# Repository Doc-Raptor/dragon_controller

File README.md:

This is a controller-board for 3d printers from china which are based on the anet printers and using an 8-bit board with 
on-board stepper driver and sometimes no fuse-protection (and no thermal-run-away).
This board is a low cost replacement with an stm32f103ret and socketed stepper drivers.
It is also capable of runnung from 24v.

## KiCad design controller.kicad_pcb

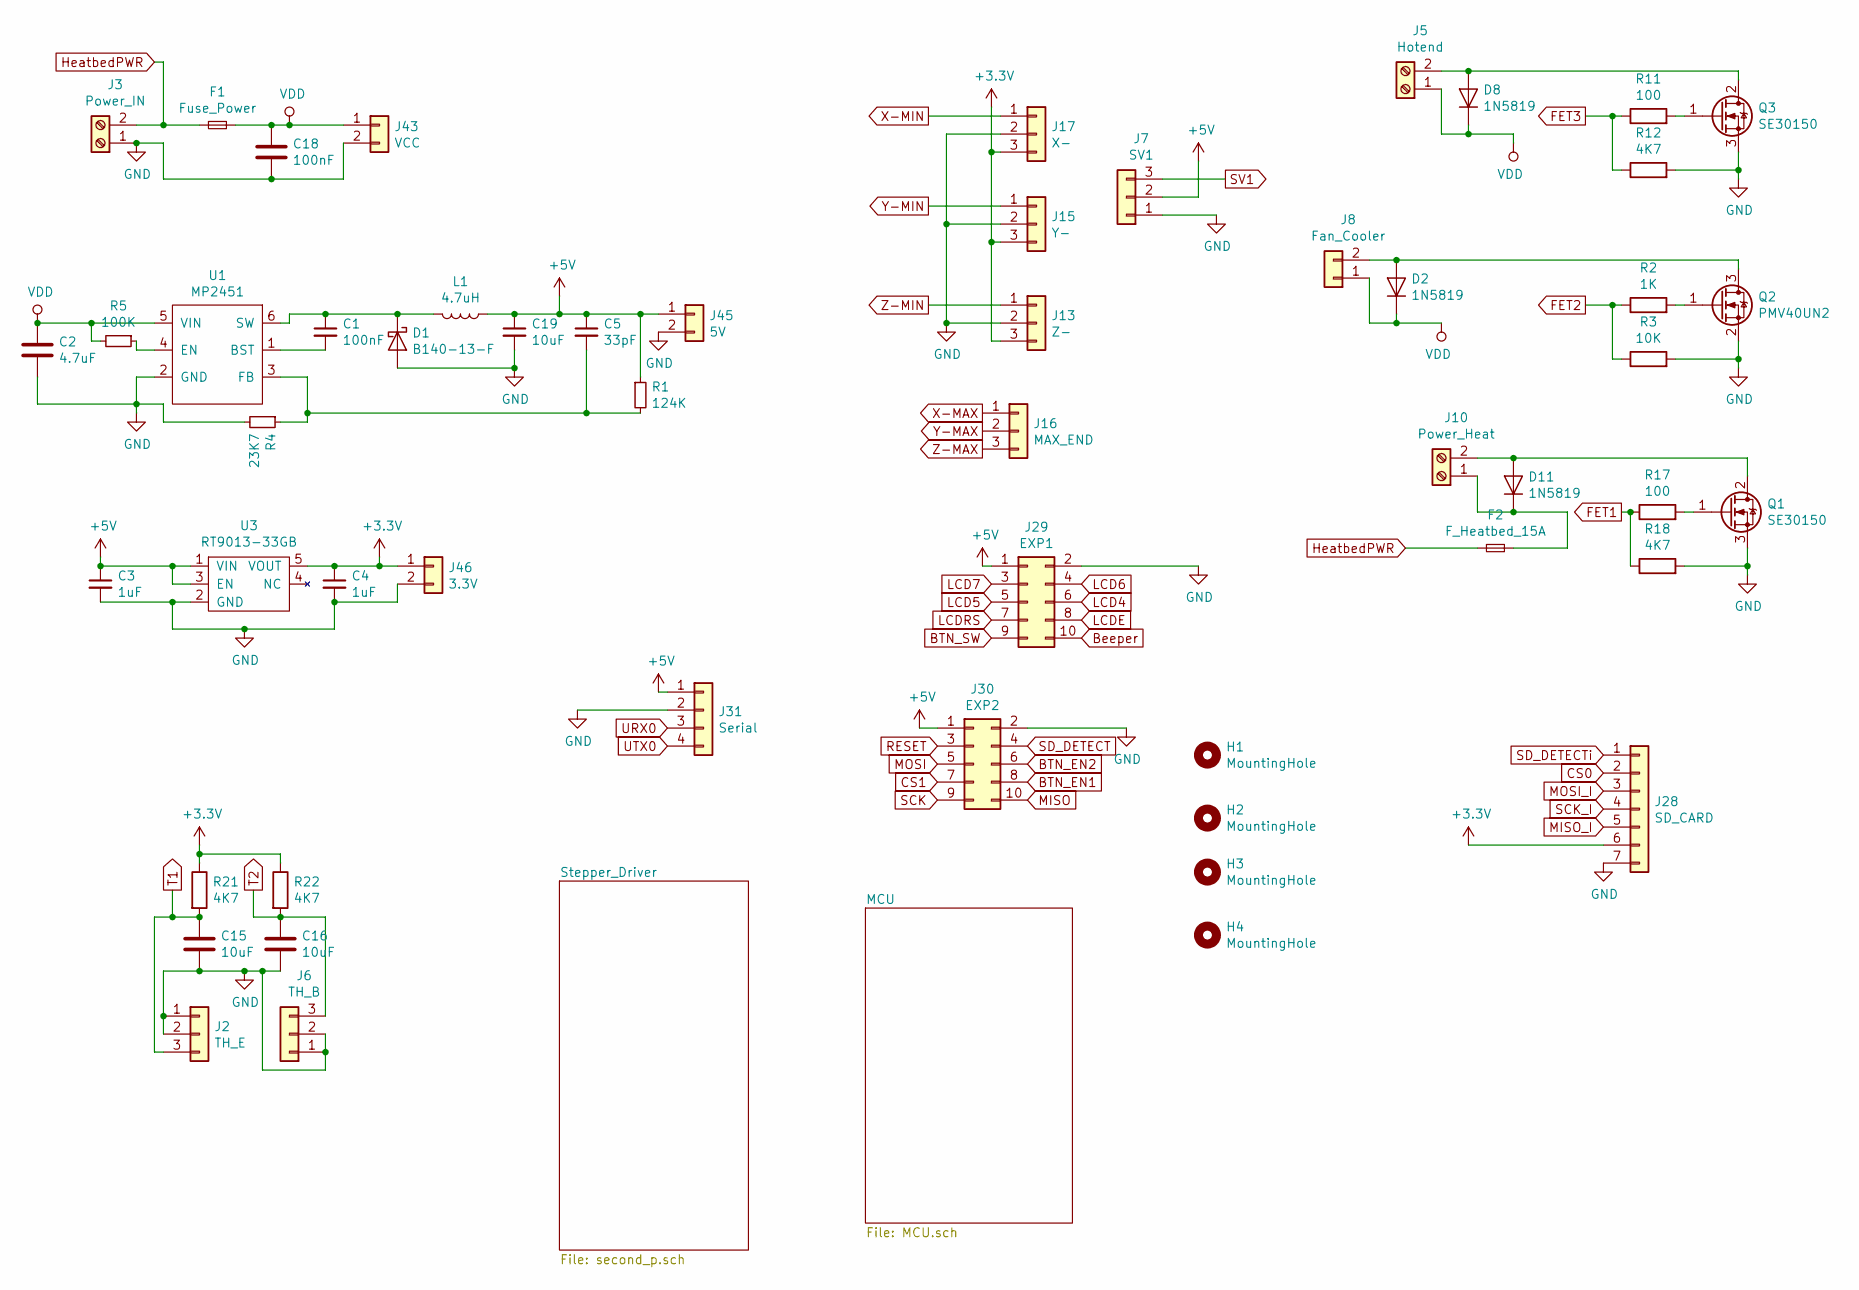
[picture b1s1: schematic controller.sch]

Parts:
C1, C18: 100nF; C_1206_3216Metric
C2: 4.7uF; C_1206_3216Metric
C3, C4: 1uF; C_0805_2012Metric
C5: 33pF; C_0603_1608Metric
C15, C16, C19: 10uF; C_1206_3216Metric
D1: B140-13-F; D_SMA
D2, D8, D11: 1N5819; D_SOD-123
F1: Fuse_Power; Fuseholder_Blade_ATO_Littelfuse_Pudenz_2_Pin
F2: F_Heatbed_15A; Fuseholder_Blade_ATO_Littelfuse_Pudenz_2_Pin
H1, H2, H3, H4: MountingHole; MountingHole_3.2mm_M3
J2: TH_E; PinHeader_1x03_P2.54mm_Vertical
J3: Power_IN; PhoenixContact_GMSTBVA_2,5_2-G-7,62_1x02_P7.62mm_Vertical
J5: Hotend; PhoenixContact_MCV_1,5_2-G-5.08_1x02_P5.08mm_Vertical
J6: TH_B; PinHeader_1x03_P2.54mm_Vertical
J7: SV1; PinHeader_1x03_P2.54mm_Vertical
J8: Fan_Cooler; PinHeader_1x02_P2.54mm_Vertical
J10: Power_Heat; PhoenixContact_GMSTBVA_2,5_2-G-7,62_1x02_P7.62mm_Vertical
J13: Z-; PinHeader_1x03_P2.54mm_Vertical
J15: Y-; PinHeader_1x03_P2.54mm_Vertical
J16: MAX_END; PinHeader_1x03_P2.54mm_Vertical
J17: X-; PinHeader_1x03_P2.54mm_Vertical
J28: SD_CARD; PinHeader_1x07_P2.54mm_Vertical
J29: EXP1; PinHeader_2x05_P2.54mm_Vertical
J30: EXP2; PinHeader_2x05_P2.54mm_Vertical
J31: Serial; PinHeader_1x04_P2.54mm_Vertical
J43: VCC; PinHeader_1x02_P2.54mm_Vertical
J45: 5V; PinHeader_1x02_P2.54mm_Vertical
J46: 3.3V; PinHeader_1x02_P2.54mm_Vertical
L1: 4.7uH; L_1812_4532Metric
Q1, Q3: SE30150; TO-263-3_TabPin2
Q2: PMV40UN2; SOT-23
R1: 124K; R_1206_3216Metric
R2: 1K; R_1206_3216Metric
R3: 10K; R_1206_3216Metric
R4: 23K7; R_1206_3216Metric
R5: 100K; R_1206_3216Metric
R11, R17: 100; R_1206_3216Metric
R12, R18, R21, R22: 4K7; R_1206_3216Metric
U1: MP2451; SOT-23-6
U3: RT9013-33GB; SOT-23-5

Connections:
+3V3: C4.1, J13.3, J15.3, J17.3, J28.6, J46.1, R21.1, R22.1, U3.5 (VOUT); also elsewhere on the board
+5V: C3.1, C5.1, C19.1, J7.2, J29.1, J30.1, J31.1, J45.1, L1.1, R1.1, U3.1 (VIN), U3.3 (EN)
BTN_EN1: J30.8; also elsewhere on the board
BTN_EN2: J30.6; also elsewhere on the board
BTN_SW: J29.9; also elsewhere on the board
Beeper: J29.10; also elsewhere on the board
CS0: J28.2; also elsewhere on the board
CS1: J30.7; also elsewhere on the board
FET1: R17.1, R18.1; also elsewhere on the board
FET2: R2.1, R3.1; also elsewhere on the board
FET3: R11.1, R12.1; also elsewhere on the board
GND: C2.2, C3.2, C4.2, C15.2, C16.2, C18.2, C19.2, D1.2 (A), J2.1, J2.2, J3.1, J6.1, J6.2, J7.1, J13.2, J15.2, J17.2, J28.7, J29.2, J30.2, J31.2, J43.2, J45.2, J46.2, Q1.3 (S), Q2.2 (S), Q3.3 (S), R3.2, R4.2, R12.2, R18.2, U1.2 (GND), U3.2 (GND); also elsewhere on the board
HeatbedPWR: F1.1, F2.1, J3.2
LCD4: J29.6; also elsewhere on the board
LCD5: J29.5; also elsewhere on the board
LCD6: J29.4; also elsewhere on the board
LCD7: J29.3; also elsewhere on the board
LCDE: J29.8; also elsewhere on the board
LCDRS: J29.7; also elsewhere on the board
MISO: J30.10; also elsewhere on the board
MISO_I: J28.5; also elsewhere on the board
MOSI: J30.5; also elsewhere on the board
MOSI_I: J28.3; also elsewhere on the board
unnamed: C1.1, D1.1 (K), L1.2, U1.6 (SW)
unnamed: C1.2, U1.1 (BST)
unnamed: C5.2, R1.2, R4.1, U1.3 (FB)
unnamed: D2.2 (A), J8.2, Q2.3 (D)
unnamed: D8.2 (A), J5.2, Q3.2 (D)
unnamed: D11.1 (K), F2.2, J10.1
unnamed: D11.2 (A), J10.2, Q1.2 (D)
unnamed: Q1.1 (G), R17.2
unnamed: Q2.1 (G), R2.2
unnamed: Q3.1 (G), R11.2
unnamed: R5.1, U1.4 (EN)
RESET: J30.3; also elsewhere on the board
SCK: J30.9; also elsewhere on the board
SCK_I: J28.4; also elsewhere on the board
SD_DETECT: J30.4; also elsewhere on the board
SD_DETECTi: J28.1; also elsewhere on the board
SV1: J7.3; also elsewhere on the board
T1: C15.1, J2.3, R21.2; also elsewhere on the board
T2: C16.1, J6.3, R22.2; also elsewhere on the board
URX0: J31.3; also elsewhere on the board
UTX0: J31.4; also elsewhere on the board
VDD: C2.1, C18.1, D2.1 (K), D8.1 (K), F1.2, J5.1, J8.1, J43.1, R5.2, U1.5 (VIN); also elsewhere on the board
X-MAX: J16.1; also elsewhere on the board
X-MIN: J17.1; also elsewhere on the board
Y-MAX: J16.2; also elsewhere on the board
Y-MIN: J15.1; also elsewhere on the board
Z-MAX: J16.3; also elsewhere on the board
Z-MIN: J13.1; also elsewhere on the board

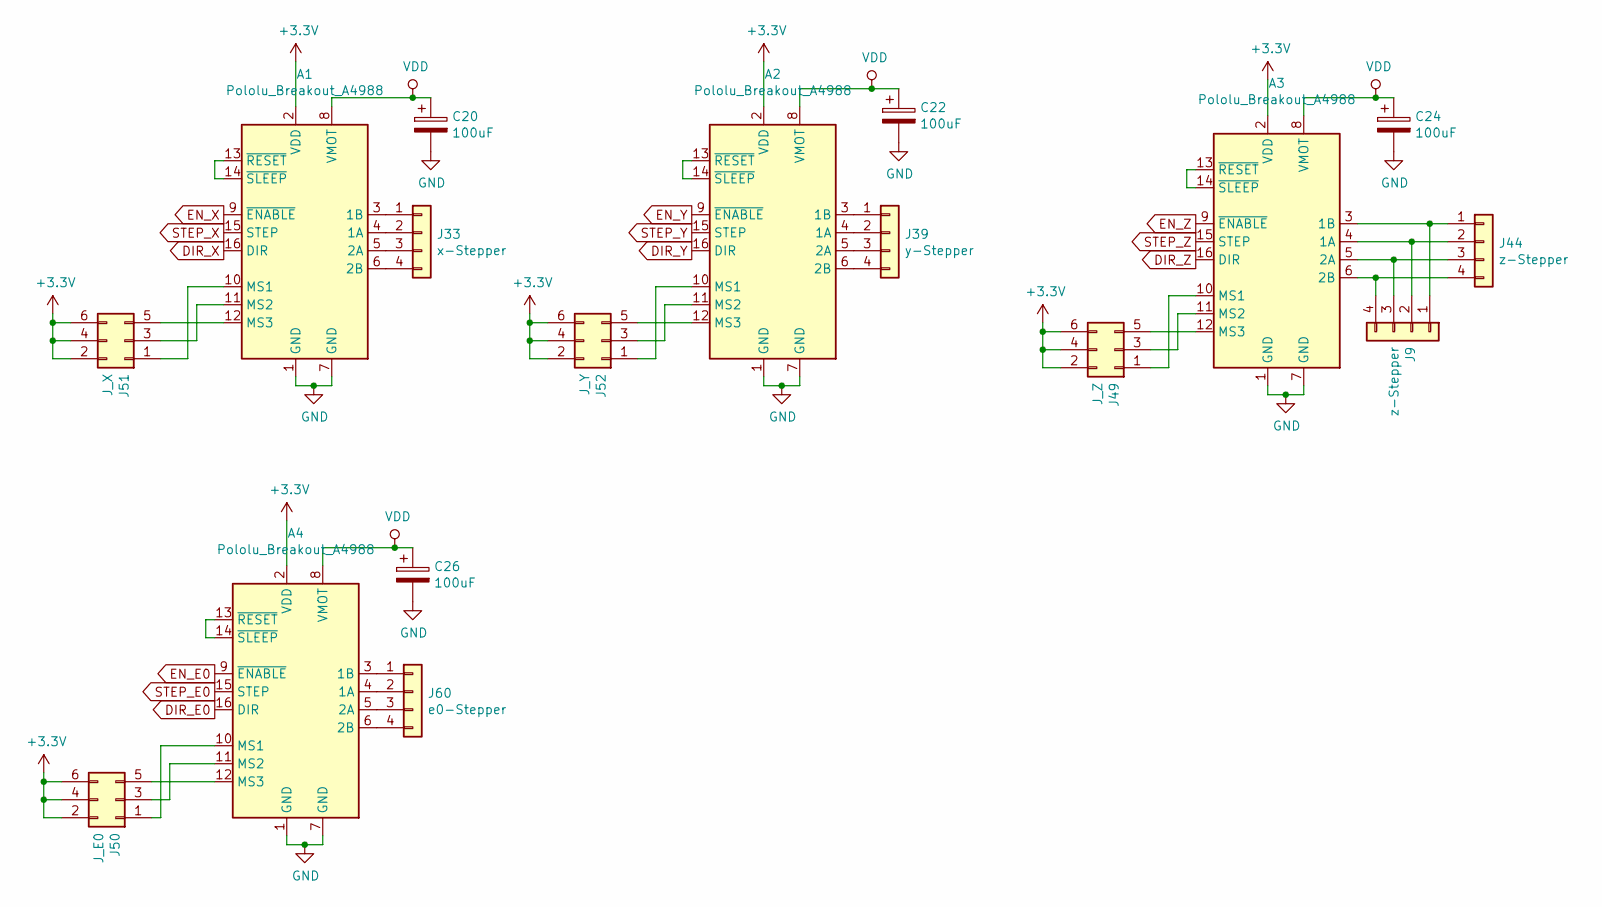
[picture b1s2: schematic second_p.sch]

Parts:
A1, A2, A3, A4: Pololu_Breakout_A4988; Pololu_Breakout-16_15.2x20.3mm
C20, C22, C24, C26: 100uF; CP_Elec_6.3x7.7
J9, J44: z-Stepper; PinHeader_1x04_P2.54mm_Vertical
J33: x-Stepper; PinHeader_1x04_P2.54mm_Vertical
J39: y-Stepper; PinHeader_1x04_P2.54mm_Vertical
J49: J_Z; PinHeader_2x03_P2.54mm_Vertical
J50: J_E0; PinHeader_2x03_P2.54mm_Vertical
J51: J_X; PinHeader_2x03_P2.54mm_Vertical
J52: J_Y; PinHeader_2x03_P2.54mm_Vertical
J60: e0-Stepper; PinHeader_1x04_P2.54mm_Vertical

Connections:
+3V3: A1.2 (VDD), A2.2 (VDD), A3.2 (VDD), A4.2 (VDD), J49.2, J49.4, J49.6, J50.2, J50.4, J50.6, J51.2, J51.4, J51.6, J52.2, J52.4, J52.6; also elsewhere on the board
DIR_E0: A4.16 (DIR); also elsewhere on the board
DIR_X: A1.16 (DIR); also elsewhere on the board
DIR_Y: A2.16 (DIR); also elsewhere on the board
DIR_Z: A3.16 (DIR); also elsewhere on the board
EN_E0: A4.9 (~ENABLE); also elsewhere on the board
EN_X: A1.9 (~ENABLE); also elsewhere on the board
EN_Y: A2.9 (~ENABLE); also elsewhere on the board
EN_Z: A3.9 (~ENABLE); also elsewhere on the board
GND: A1.1 (GND), A1.7 (GND), A2.1 (GND), A2.7 (GND), A3.1 (GND), A3.7 (GND), A4.1 (GND), A4.7 (GND), C20.2, C22.2, C24.2, C26.2; also elsewhere on the board
unnamed: A1.3 (1B), J33.1
unnamed: A1.4 (1A), J33.2
unnamed: A1.5 (2A), J33.3
unnamed: A1.6 (2B), J33.4
unnamed: A1.10 (MS1), J51.1
unnamed: A1.11 (MS2), J51.3
unnamed: A1.12 (MS3), J51.5
unnamed: A1.13 (~RESET), A1.14 (~SLEEP)
unnamed: A2.3 (1B), J39.1
unnamed: A2.4 (1A), J39.2
unnamed: A2.5 (2A), J39.3
unnamed: A2.6 (2B), J39.4
unnamed: A2.10 (MS1), J52.1
unnamed: A2.11 (MS2), J52.3
unnamed: A2.12 (MS3), J52.5
unnamed: A2.13 (~RESET), A2.14 (~SLEEP)
unnamed: A3.3 (1B), J9.1, J44.1
unnamed: A3.4 (1A), J9.2, J44.2
unnamed: A3.5 (2A), J9.3, J44.3
unnamed: A3.6 (2B), J9.4, J44.4
unnamed: A3.10 (MS1), J49.1
unnamed: A3.11 (MS2), J49.3
unnamed: A3.12 (MS3), J49.5
unnamed: A3.13 (~RESET), A3.14 (~SLEEP)
unnamed: A4.3 (1B), J60.1
unnamed: A4.4 (1A), J60.2
unnamed: A4.5 (2A), J60.3
unnamed: A4.6 (2B), J60.4
unnamed: A4.10 (MS1), J50.1
unnamed: A4.11 (MS2), J50.3
unnamed: A4.12 (MS3), J50.5
unnamed: A4.13 (~RESET), A4.14 (~SLEEP)
STEP_E0: A4.15 (STEP); also elsewhere on the board
STEP_X: A1.15 (STEP); also elsewhere on the board
STEP_Y: A2.15 (STEP); also elsewhere on the board
STEP_Z: A3.15 (STEP); also elsewhere on the board
VDD: A1.8 (VMOT), A2.8 (VMOT), A3.8 (VMOT), A4.8 (VMOT), C20.1, C22.1, C24.1, C26.1; also elsewhere on the board

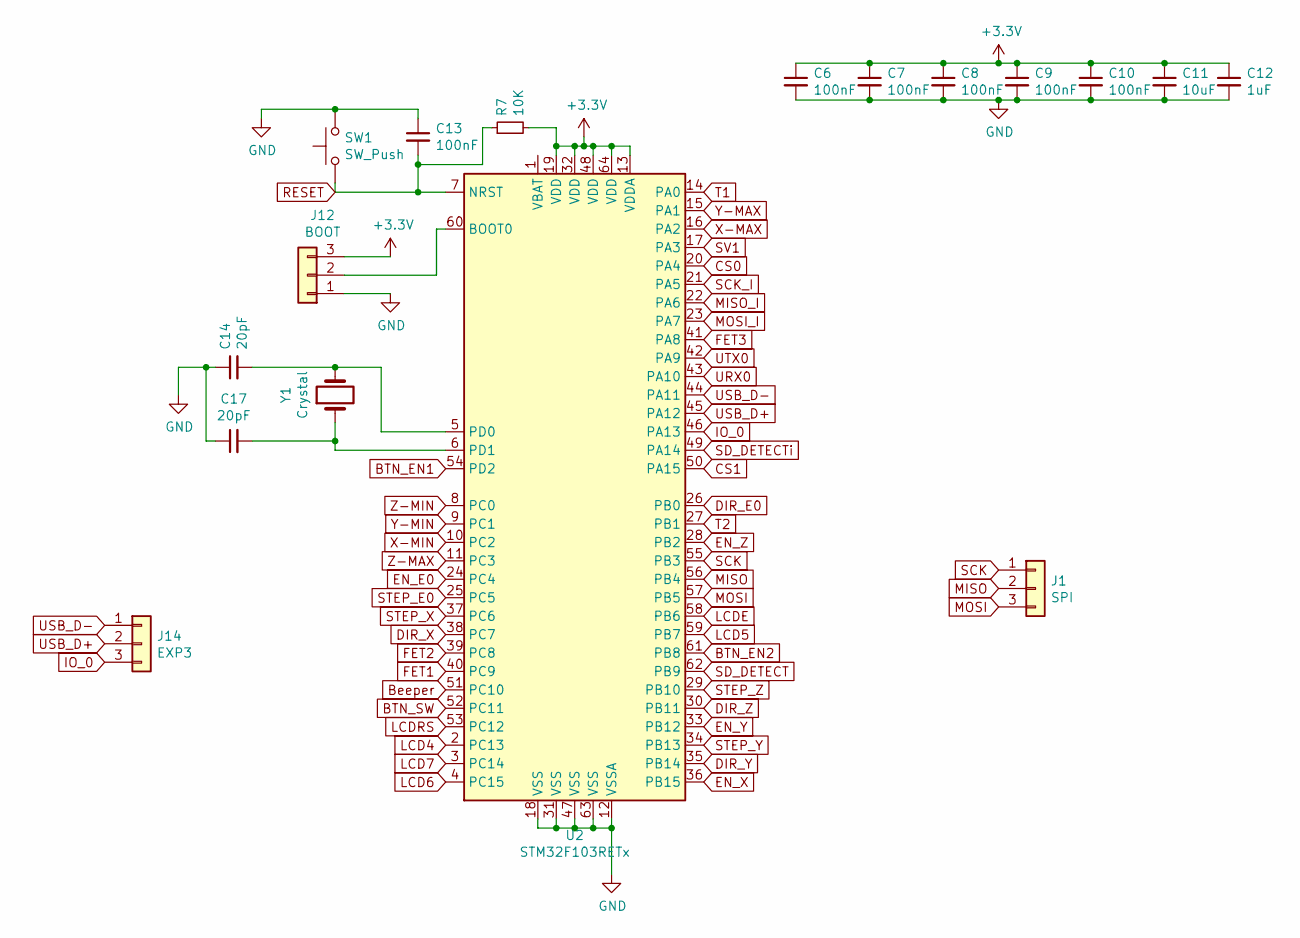
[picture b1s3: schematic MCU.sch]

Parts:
C6, C7, C8, C9, C10, C13: 100nF; C_1206_3216Metric
C11: 10uF; C_1206_3216Metric
C12: 1uF; C_0805_2012Metric
C14, C17: 20pF; C_0603_1608Metric
J1: SPI; PinHeader_1x03_P2.54mm_Vertical
J12: BOOT; PinHeader_1x03_P2.54mm_Vertical
J14: EXP3; PinHeader_1x03_P2.54mm_Vertical
R7: 10K; R_1206_3216Metric
SW1: SW_Push; SW_Push_SPST_NO_Alps_SKRK
U2: STM32F103RETx; LQFP-64_10x10mm_P0.5mm
Y1: Crystal; Crystal_SMD_5032-2Pin_5.0x3.2mm

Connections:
+3V3: C6.1, C7.1, C8.1, C9.1, C10.1, C11.1, C12.1, J12.3, R7.2, U2.13 (VDDA), U2.19 (VDD), U2.32 (VDD), U2.48 (VDD), U2.64 (VDD); also elsewhere on the board
BTN_EN1: U2.54 (PD2); also elsewhere on the board
BTN_EN2: U2.61 (PB8); also elsewhere on the board
BTN_SW: U2.52 (PC11); also elsewhere on the board
Beeper: U2.51 (PC10); also elsewhere on the board
CS0: U2.20 (PA4); also elsewhere on the board
CS1: U2.50 (PA15); also elsewhere on the board
DIR_E0: U2.26 (PB0); also elsewhere on the board
DIR_X: U2.38 (PC7); also elsewhere on the board
DIR_Y: U2.35 (PB14); also elsewhere on the board
DIR_Z: U2.30 (PB11); also elsewhere on the board
EN_E0: U2.24 (PC4); also elsewhere on the board
EN_X: U2.36 (PB15); also elsewhere on the board
EN_Y: U2.33 (PB12); also elsewhere on the board
EN_Z: U2.28 (PB2); also elsewhere on the board
FET1: U2.40 (PC9); also elsewhere on the board
FET2: U2.39 (PC8); also elsewhere on the board
FET3: U2.41 (PA8); also elsewhere on the board
GND: C6.2, C7.2, C8.2, C9.2, C10.2, C11.2, C12.2, C13.1, C14.1, C17.1, J12.1, SW1.2, U2.12 (VSSA), U2.18 (VSS), U2.31 (VSS), U2.47 (VSS), U2.63 (VSS); also elsewhere on the board
IO_0: J14.3, U2.46 (PA13)
LCD4: U2.2 (PC13); also elsewhere on the board
LCD5: U2.59 (PB7); also elsewhere on the board
LCD6: U2.4 (PC15); also elsewhere on the board
LCD7: U2.3 (PC14); also elsewhere on the board
LCDE: U2.58 (PB6); also elsewhere on the board
LCDRS: U2.53 (PC12); also elsewhere on the board
MISO: J1.2, U2.56 (PB4); also elsewhere on the board
MISO_I: U2.22 (PA6); also elsewhere on the board
MOSI: J1.3, U2.57 (PB5); also elsewhere on the board
MOSI_I: U2.23 (PA7); also elsewhere on the board
unnamed: C14.2, U2.5 (PD0), Y1.2
unnamed: C17.2, U2.6 (PD1), Y1.1
unnamed: J12.2, U2.60 (BOOT0)
RESET: C13.2, R7.1, SW1.1, U2.7 (NRST); also elsewhere on the board
SCK: J1.1, U2.55 (PB3); also elsewhere on the board
SCK_I: U2.21 (PA5); also elsewhere on the board
SD_DETECT: U2.62 (PB9); also elsewhere on the board
SD_DETECTi: U2.49 (PA14); also elsewhere on the board
STEP_E0: U2.25 (PC5); also elsewhere on the board
STEP_X: U2.37 (PC6); also elsewhere on the board
STEP_Y: U2.34 (PB13); also elsewhere on the board
STEP_Z: U2.29 (PB10); also elsewhere on the board
SV1: U2.17 (PA3); also elsewhere on the board
T1: U2.14 (PA0); also elsewhere on the board
T2: U2.27 (PB1); also elsewhere on the board
URX0: U2.43 (PA10); also elsewhere on the board
USB_D+: J14.2, U2.45 (PA12)
USB_D-: J14.1, U2.44 (PA11)
UTX0: U2.42 (PA9); also elsewhere on the board
X-MAX: U2.16 (PA2); also elsewhere on the board
X-MIN: U2.10 (PC2); also elsewhere on the board
Y-MAX: U2.15 (PA1); also elsewhere on the board
Y-MIN: U2.9 (PC1); also elsewhere on the board
Z-MAX: U2.11 (PC3); also elsewhere on the board
Z-MIN: U2.8 (PC0); also elsewhere on the board

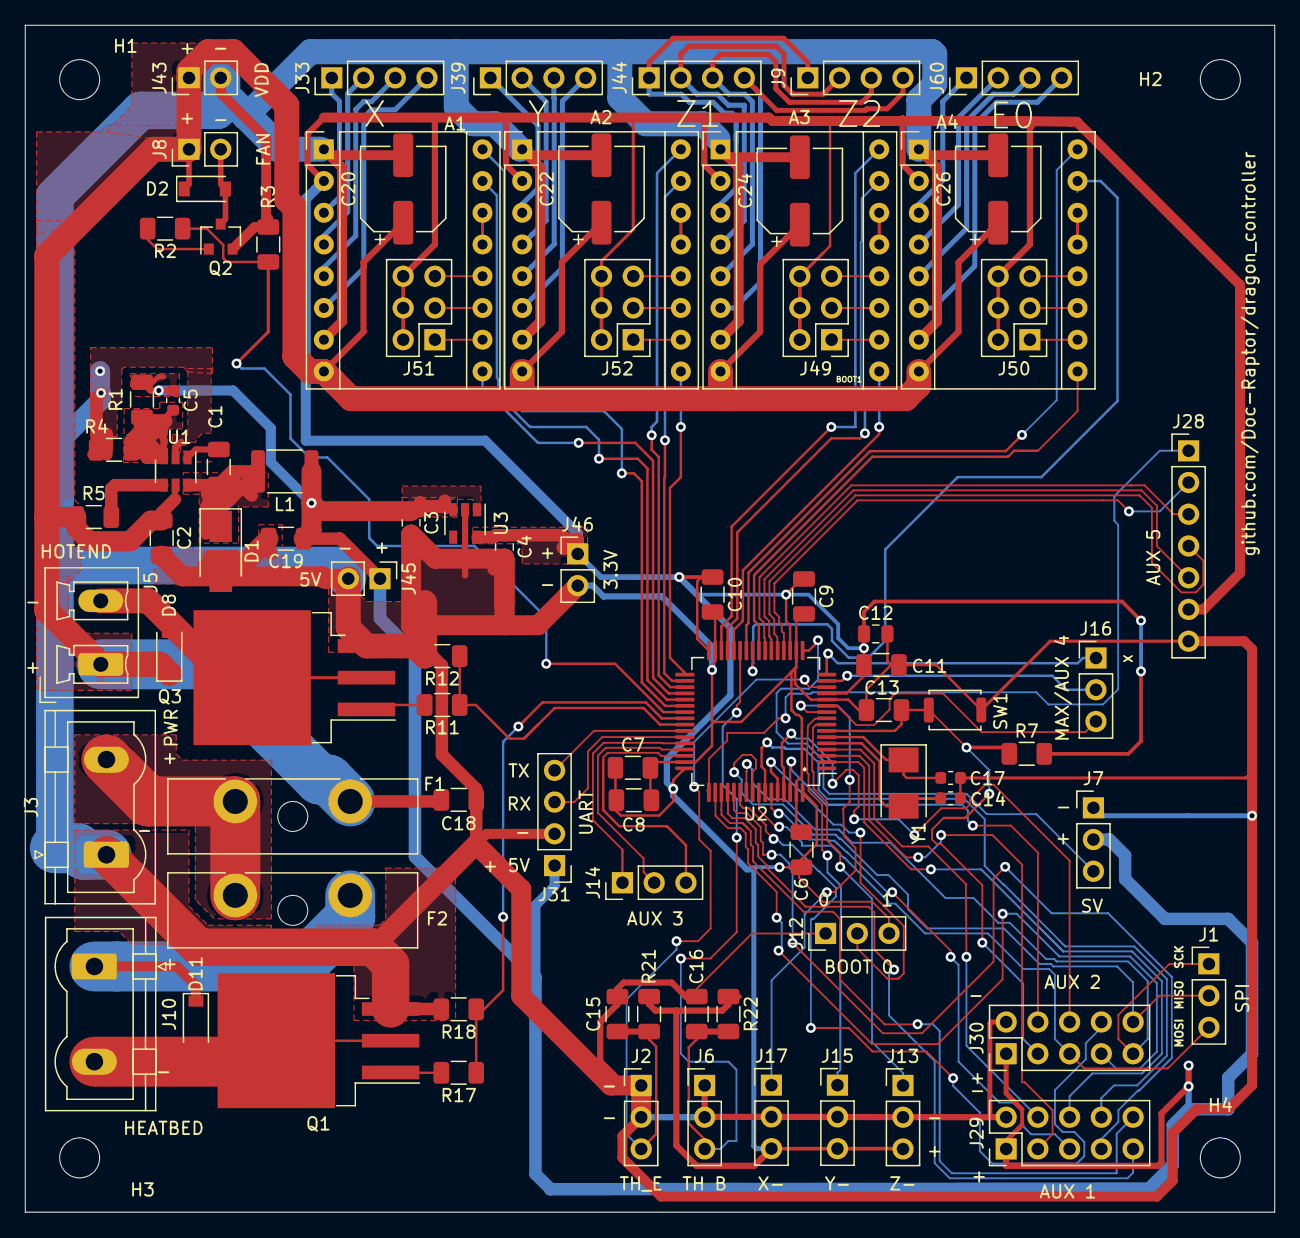
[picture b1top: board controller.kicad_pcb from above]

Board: 2 copper layers, 100.0 x 95.0 mm, 88 parts (0 on the bottom side), 101 nets.

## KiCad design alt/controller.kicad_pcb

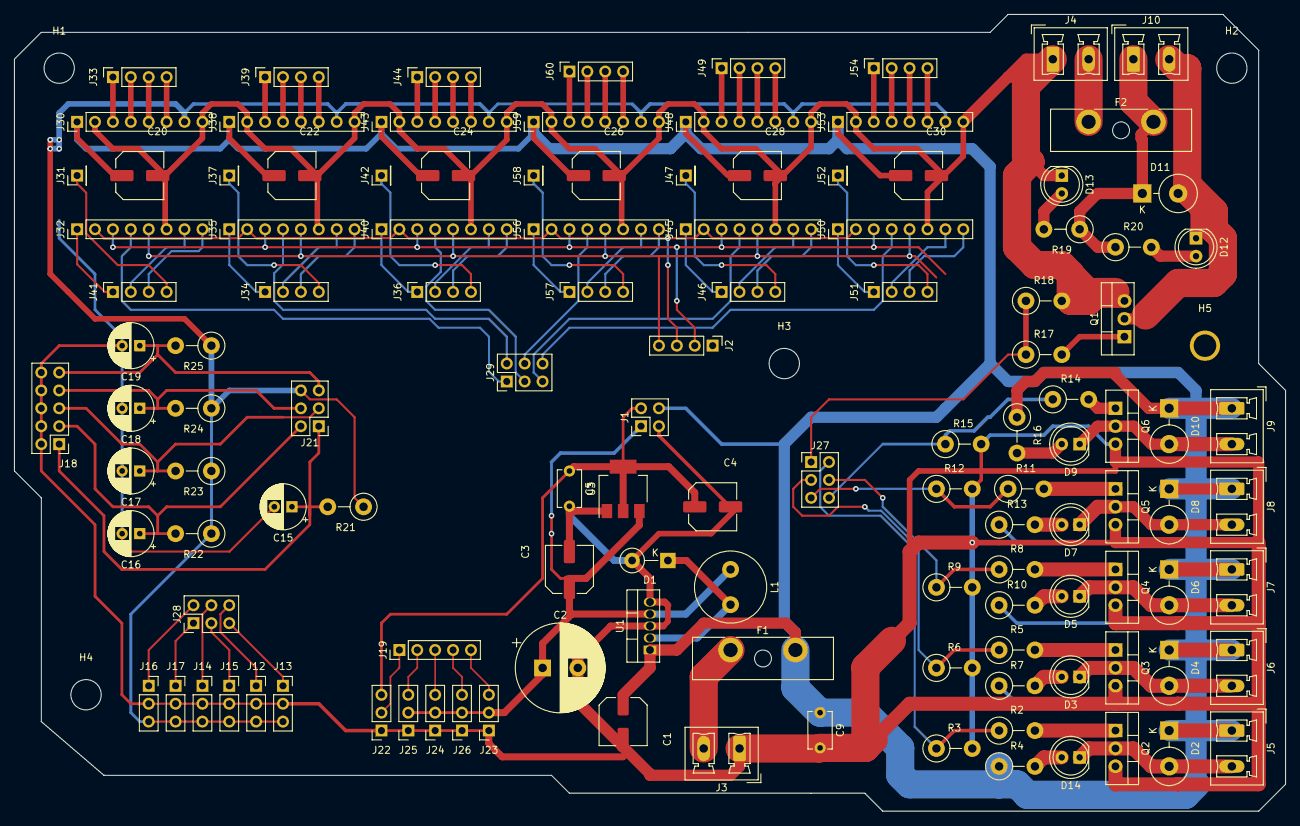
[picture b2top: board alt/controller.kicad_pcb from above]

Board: 2 copper layers, 180.3 x 113.0 mm, 128 parts (0 on the bottom side), 107 nets.

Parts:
C1, C3, C4, C20, C22, C24, C26, C28, C30: 100uF; C_Elec_6.3x7.7
C2: 330uF; CP_Radial_D12.5mm_P5.00mm
C5, C9: 100nF; C_Disc_D5.1mm_W3.2mm_P5.00mm
C15, C16, C17, C18, C19: 10uF; CP_Radial_D6.3mm_P2.50mm
D1: 1N5819; D_DO-41_SOD81_P5.08mm_Vertical_KathodeUp
D2, D4, D6, D8, D10, D11: SB5100; D_DO-201_P5.08mm_Vertical_KathodeUp
D3, D5, D7, D9, D12, D13, D14: LED; LED_D5.0mm
F1: Fuse_Power; Fuseholder_Blade_ATO_Littelfuse_Pudenz_2_Pin
F2: F_Heatbed_15A; Fuseholder_Blade_ATO_Littelfuse_Pudenz_2_Pin
H1, H2, H3, H4, H5: MountingHole; MountingHole_4.3mm_M4
J1: Power; PinHeader_2x02_P2.54mm_Vertical
J2: SPI; PinHeader_1x04_P2.54mm_Vertical
J3: Power_IN; PhoenixContact_MCV_1,5_2-G-5.08_1x02_P5.08mm_Vertical
J4: Heatbed_Power_In; PhoenixContact_MCV_1,5_2-G-5.08_1x02_P5.08mm_Vertical
J5: Power_1; PhoenixContact_MCV_1,5_2-G-5.08_1x02_P5.08mm_Vertical
J6: Power_2; PhoenixContact_MCV_1,5_2-G-5.08_1x02_P5.08mm_Vertical
J7: Power_3; PhoenixContact_MCV_1,5_2-G-5.08_1x02_P5.08mm_Vertical
J8: Power_4; PhoenixContact_MCV_1,5_2-G-5.08_1x02_P5.08mm_Vertical
J9: Power_5; PhoenixContact_MCV_1,5_2-G-5.08_1x02_P5.08mm_Vertical
J10: Power_Heat; PhoenixContact_MCV_1,5_2-G-5.08_1x02_P5.08mm_Vertical
J12: Z+; PinSocket_1x03_P2.54mm_Vertical
J13: Z-; PinSocket_1x03_P2.54mm_Vertical
J14: Y+; PinSocket_1x03_P2.54mm_Vertical
J15: Y-; PinSocket_1x03_P2.54mm_Vertical
J16: X+; PinSocket_1x03_P2.54mm_Vertical
J17: X-; PinSocket_1x03_P2.54mm_Vertical
J18: Thermistor; PinHeader_2x05_P2.54mm_Vertical
J19: SV; PinHeader_1x05_P2.54mm_Vertical
J21: Thermistor+LPW; PinHeader_2x03_P2.54mm_Vertical
J22: SV1; PinSocket_1x03_P2.54mm_Vertical
J23: SV5; PinSocket_1x03_P2.54mm_Vertical
J24: SV3; PinSocket_1x03_P2.54mm_Vertical
J25: SV2; PinSocket_1x03_P2.54mm_Vertical
J26: SV4; PinSocket_1x03_P2.54mm_Vertical
J27: FET; PinHeader_2x03_P2.54mm_Vertical
J28: ENDSTOP; PinHeader_2x03_P2.54mm_Vertical
J29: CS_SPI; PinHeader_2x03_P2.54mm_Vertical
J30: x-Step_High; PinHeader_1x08_P2.54mm_Vertical
J31: Dia_x; PinHeader_1x01_P2.54mm_Vertical
J32: x-Step_Low; PinHeader_1x08_P2.54mm_Vertical
J33: x-Stepper; PinSocket_1x04_P2.54mm_Vertical
J34: Y_STEP; PinSocket_1x04_P2.54mm_Vertical
J35: y-Step_Low; PinHeader_1x08_P2.54mm_Vertical
J36: Z_STEP; PinSocket_1x04_P2.54mm_Vertical
J37: Dia_y; PinHeader_1x01_P2.54mm_Vertical
J38: y-Step_High; PinHeader_1x08_P2.54mm_Vertical
J39: y-Stepper; PinSocket_1x04_P2.54mm_Vertical
J40: z-Step_Low; PinHeader_1x08_P2.54mm_Vertical
J41: X_STEP; PinSocket_1x04_P2.54mm_Vertical
J42: Dia_z; PinHeader_1x01_P2.54mm_Vertical
J43: z-Step_High; PinHeader_1x08_P2.54mm_Vertical
J44: z-Stepper; PinSocket_1x04_P2.54mm_Vertical
J45: e2-Step_Low; PinHeader_1x08_P2.54mm_Vertical
J46: E2_STEP; PinSocket_1x04_P2.54mm_Vertical
J47: Dia_e2; PinHeader_1x01_P2.54mm_Vertical
J48: e2-Step_High; PinHeader_1x08_P2.54mm_Vertical
J49: e2-Stepper; PinSocket_1x04_P2.54mm_Vertical
J50: e3-Step_Low; PinHeader_1x08_P2.54mm_Vertical
J51: E3_STEP; PinSocket_1x04_P2.54mm_Vertical
J52: Dia_e3; PinHeader_1x01_P2.54mm_Vertical
J53: e3-Step_High; PinHeader_1x08_P2.54mm_Vertical
J54: e3-Stepper; PinSocket_1x04_P2.54mm_Vertical
J56: e1-Step_Low; PinHeader_1x08_P2.54mm_Vertical
J57: E1_STEP; PinSocket_1x04_P2.54mm_Vertical
J58: Dia_e1; PinHeader_1x01_P2.54mm_Vertical
J59: e1-Step_High; PinHeader_1x08_P2.54mm_Vertical
J60: e1-Stepper; PinSocket_1x04_P2.54mm_Vertical
L1: 330uH; L_Radial_D10.0mm_P5.00mm_Neosid_SD12_style3
Q1: NXP BUK954R8-60E; TO-220-3_Vertical
Q2, Q3, Q4, Q5, Q6: IRF3708; TO-220-3_Vertical
R2, R5, R8, R11, R14, R17: 100; R_Axial_DIN0411_L9.9mm_D3.6mm_P5.08mm_Vertical
R3, R6, R9, R12, R15, R18: 33K; R_Axial_DIN0411_L9.9mm_D3.6mm_P5.08mm_Vertical
R4, R7, R10, R13, R16, R19, R20: 1K8; R_Axial_DIN0411_L9.9mm_D3.6mm_P5.08mm_Vertical
R21, R22, R23, R24, R25: 4K7; R_Axial_DIN0411_L9.9mm_D3.6mm_P5.08mm_Vertical
U1: LM2575-5.0BT; TO-220-5_Vertical
U3: AMS1117-3.3; SOT-223-3_TabPin2

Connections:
+3V3: C4.1, C5.1, J1.2, J22.3, U3.2
+5V: C2.1, C3.1, J1.1, J23.2, J24.2, J25.2, J26.2, L1.1, U1.4, U3.3
CLK: J2.2, J32.3, J35.3, J40.3, J45.3, J50.3, J56.3
CS0: J29.1, J32.4
CS1: J29.2, J35.4
CS2: J29.3, J40.4
CS3: J29.4, J56.4
CS4: J29.5, J45.4
CS5: J29.6, J50.4
DIR_E1: J56.8, J57.3
DIR_E2: J45.8, J46.3
DIR_E3: J50.8, J51.3
DIR_X: J32.8, J41.3
DIR_Y: J34.3, J35.8
DIR_Z: J36.3, J40.8
D_E1: J57.4, J58.1
D_E2: J46.4, J47.1
D_E3: J51.4, J52.1
D_X: J31.1, J41.4
D_Y: J34.4, J37.1
D_Z: J36.4, J42.1
EN_E1: J56.1, J57.1
EN_E2: J45.1, J46.1
EN_E3: J50.1, J51.1
EN_X: J32.1, J41.1
EN_Y: J34.1, J35.1
EN_Z: J36.1, J40.1
FET1: J27.1, R17.1, R18.1
FET2: J27.2, R2.1, R3.1
FET3: J27.3, R5.1, R6.1
FET4: J27.4, R8.1, R9.1
FET5: J27.5, R11.1, R12.1
FET6: J27.6, R14.1, R15.1
GND: C1.2, C2.2, C3.2, C4.2, C5.2, C9.2, C15.2, C16.2, C17.2, C18.2, C19.2, C20.2, C22.2, C24.2, C26.2, C28.2, C30.2, D1.2, D13.1, J1.3, J3.1, J4.1, J12.2, J13.2, J14.2, J15.2, J16.2, J17.2, J18.2, J18.4, J18.6, J18.8, J18.10, J22.1, J23.1, J24.1, J25.1, J26.1, J30.2, J30.8, J32.6, J35.6, J38.2, J38.8, J40.6, J43.2, J43.8, J45.6, J48.2, J48.8, J50.6, J53.2, J53.8, J56.6, J59.2, J59.8, Q1.3, Q2.3, Q3.3, Q4.3, Q5.3, Q6.3, R3.2, R6.2, R9.2, R12.2, R15.2, R18.2, U1.3, U1.5, U3.1
LOGIC_PW: J12.3, J13.3, J14.3, J15.3, J16.3, J17.3, J21.6, J30.7, J38.7, J43.7, J48.7, J53.7, J59.7, R21.1, R22.1, R23.1, R24.1, R25.1
MISO: J2.4, J32.5, J35.5, J40.5, J45.5, J50.5, J56.5
MOSI: J2.3, J32.2, J35.2, J40.2, J45.2, J50.2, J56.2
unnamed: D1.1, L1.2, U1.2
unnamed: D3.1, D4.2, J6.2, Q3.2
unnamed: D3.2, R7.2
unnamed: D5.1, D6.2, J7.2, Q4.2
unnamed: D5.2, R10.2
unnamed: D7.1, D8.2, J8.2, Q5.2
unnamed: D7.2, R13.2
unnamed: D9.2, R16.2
unnamed: D9.1, D10.2, J9.2, Q6.2
unnamed: D11.1, F2.2, J10.1, R19.1, R20.1
unnamed: D11.2, D12.1, J10.2, Q1.2
unnamed: D12.2, R20.2
unnamed: D13.2, R19.2
unnamed: D2.2, D14.1, J5.2, Q2.2
unnamed: D14.2, R4.2
unnamed: F1.1, J3.2
unnamed: F2.1, J4.2
unnamed: J30.3, J33.1
unnamed: J30.4, J33.2
unnamed: J30.5, J33.3
unnamed: J30.6, J33.4
unnamed: J38.3, J39.1
unnamed: J38.4, J39.2
unnamed: J38.5, J39.3
unnamed: J38.6, J39.4
unnamed: J43.3, J44.1
unnamed: J43.4, J44.2
unnamed: J43.5, J44.3
unnamed: J43.6, J44.4
unnamed: J48.3, J49.1
unnamed: J48.4, J49.2
unnamed: J48.5, J49.3
unnamed: J48.6, J49.4
unnamed: J53.3, J54.1
unnamed: J53.4, J54.2
unnamed: J53.5, J54.3
unnamed: J53.6, J54.4
unnamed: J59.3, J60.1
unnamed: J59.4, J60.2
unnamed: J59.5, J60.3
unnamed: J59.6, J60.4
unnamed: Q1.1, R17.2
unnamed: Q2.1, R2.2
unnamed: Q3.1, R5.2
unnamed: Q4.1, R8.2
unnamed: Q5.1, R11.2
unnamed: Q6.1, R14.2
STEP_E1: J56.7, J57.2
STEP_E2: J45.7, J46.2
STEP_E3: J50.7, J51.2
STEP_X: J32.7, J41.2
STEP_Y: J34.2, J35.7
STEP_Z: J36.2, J40.7
SV1: J19.1, J22.2
SV2: J19.2, J25.3
SV3: J19.3, J24.3
SV4: J19.4, J26.3
SV5: J19.5, J23.3
T1: C15.1, J18.1, J21.1, R21.2
T2: C16.1, J18.3, J21.2, R22.2
T3: C17.1, J18.5, J21.3, R23.2
T4: C18.1, J18.7, J21.4, R24.2
T5: C19.1, J18.9, J21.5, R25.2
VDD: C1.1, C9.1, C20.1, C22.1, C24.1, C26.1, C28.1, C30.1, D2.1, D4.1, D6.1, D8.1, D10.1, F1.2, J1.4, J5.1, J6.1, J7.1, J8.1, J9.1, J30.1, J38.1, J43.1, J48.1, J53.1, J59.1, R4.1, R7.1, R10.1, R13.1, R16.1, U1.1
X-MAX: J16.1, J28.2
X-MIN: J17.1, J28.1
Y-MAX: J14.1, J28.4
Y-MIN: J15.1, J28.3
Z-MAX: J12.1, J28.6
Z-MIN: J13.1, J28.5

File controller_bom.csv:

"ID";"Bezeichner";"Gehäuse";"Stückzahl";"Bezeichnung";"Anbieter und Referenz";
1;"C1,C3,C4,C20,C22,C24,C26,C28,C30";"CP_Elec_6.3x7.7";9;"100uF";;;
2;"C2";"CP_Elec_10x14.3";1;"330uF";;;
3;"C5,C9";"C_1210_3225Metric";2;"100nF";;;
4;"C15,C16,C17,C18";"C_1210_3225Metric";4;"10uF";;;
5;"D1,D2,D4,D6,D8,D11";"D_SOD-123";6;"1N5819";;;
6;"F1";"Fuseholder_Blade_ATO_Littelfuse_Pudenz_2_Pin";1;"Fuse_Power";;;
7;"F2";"Fuseholder_Blade_ATO_Littelfuse_Pudenz_2_Pin";1;"F_Heatbed_15A";;;
8;"H1,H2,H3,H4,H5";"MountingHole_3.2mm_M3";5;"MountingHole";;;
9;"J1";"PinHeader_2x02_P2.54mm_Vertical";1;"Power";;;
10;"J3";"PhoenixContact_MCV_1,5_2-G-5.08_1x02_P5.08mm_Vertical";1;"Power_IN";;;
11;"J4";"PhoenixContact_MCV_1,5_2-G-5.08_1x02_P5.08mm_Vertical";1;"Heatbed_Power_In";;;
12;"J5";"PhoenixContact_MCV_1,5_2-G-5.08_1x02_P5.08mm_Vertical";1;"Power_1";;;
13;"J6";"PhoenixContact_MCV_1,5_2-G-5.08_1x02_P5.08mm_Vertical";1;"Power_2";;;
14;"J7";"PhoenixContact_MCV_1,5_2-G-5.08_1x02_P5.08mm_Vertical";1;"Power_3";;;
15;"J10";"PhoenixContact_MCV_1,5_2-G-5.08_1x02_P5.08mm_Vertical";1;"Power_Heat";;;
16;"J12";"PinHeader_1x03_P2.54mm_Vertical";1;"Z+";;;
17;"J13";"PinHeader_1x03_P2.54mm_Vertical";1;"Z-";;;
18;"J14";"PinHeader_1x03_P2.54mm_Vertical";1;"Y+";;;
19;"J15";"PinHeader_1x03_P2.54mm_Vertical";1;"Y-";;;
20;"J16";"PinHeader_1x03_P2.54mm_Vertical";1;"X+";;;
21;"J17";"PinHeader_1x03_P2.54mm_Vertical";1;"X-";;;
22;"J21";"PinHeader_2x03_P2.54mm_Vertical";1;"Thermistor+LPW";;;
23;"J22";"PinHeader_1x03_P2.54mm_Vertical";1;"SV1";;;
24;"J23";"PinHeader_1x03_P2.54mm_Vertical";1;"SV4";;;
25;"J24";"PinHeader_1x03_P2.54mm_Vertical";1;"SV3";;;
26;"J25";"PinHeader_1x03_P2.54mm_Vertical";1;"SV2";;;
27;"J28";"PinHeader_2x03_P2.54mm_Vertical";1;"ENDSTOP";;;
28;"J29";"PinHeader_2x03_P2.54mm_Vertical";1;"CS_SPI";;;
29;"J33";"PinHeader_1x04_P2.54mm_Vertical";1;"x-Stepper";;;
30;"J34";"PinHeader_1x04_P2.54mm_Vertical";1;"Y_STEP";;;
31;"J36";"PinHeader_1x04_P2.54mm_Vertical";1;"Z_STEP";;;
32;"J39";"PinHeader_1x04_P2.54mm_Vertical";1;"y-Stepper";;;
33;"J41";"PinHeader_1x04_P2.54mm_Vertical";1;"X_STEP";;;
34;"J44";"PinHeader_1x04_P2.54mm_Vertical";1;"z-Stepper";;;
35;"J46";"PinHeader_1x04_P2.54mm_Vertical";1;"E2_STEP";;;
36;"J49";"PinHeader_1x04_P2.54mm_Vertical";1;"e2-Stepper";;;
37;"J51";"PinHeader_1x04_P2.54mm_Vertical";1;"E3_STEP";;;
38;"J54";"PinHeader_1x04_P2.54mm_Vertical";1;"e3-Stepper";;;
39;"J57";"PinHeader_1x04_P2.54mm_Vertical";1;"E1_STEP";;;
40;"J60";"PinHeader_1x04_P2.54mm_Vertical";1;"e1-Stepper";;;
41;"L1";"L_Bourns-SRN1060";1;"330uH";;;
42;"R2";"R_1206_3216Metric";1;"1K";;;
43;"R3";"R_1206_3216Metric";1;"10K";;;
44;"R5,R8,R11,R17";"R_1206_3216Metric";4;"100";;;
45;"R6,R9,R12,R18";"R_1206_3216Metric";4;"33K";;;
46;"R21,R22,R23,R24";"R_1206_3216Metric";4;"4K7";;;
47;"U1";"TO-220-5_Vertical";1;"LM2575-5.0BT";;;
48;"U3";"SOT-223-3_TabPin2";1;"AMS1117-3.3";;;
49;"J27";"PinHeader_1x05_P2.54mm_Vertical";1;"FET";;;
50;"J2";"PinHeader_1x03_P2.54mm_Vertical";1;"SPI";;;
51;"J18";"PinHeader_2x04_P2.54mm_Vertical";1;"Thermistor";;;
52;"Q2";"SOT-23";1;"PMV40UN2";;;
53;"J30";"PinSocket_1x08_P2.54mm_Vertical";1;"x-Step_High";;;
54;"J31";"PinSocket_1x01_P2.54mm_Vertical";1;"Dia_x";;;
55;"J32";"PinSocket_1x08_P2.54mm_Vertical";1;"x-Step_Low";;;
56;"J35";"PinSocket_1x08_P2.54mm_Vertical";1;"y-Step_Low";;;
57;"J37";"PinSocket_1x01_P2.54mm_Vertical";1;"Dia_y";;;
58;"J38";"PinSocket_1x08_P2.54mm_Vertical";1;"y-Step_High";;;
59;"J40";"PinSocket_1x08_P2.54mm_Vertical";1;"z-Step_Low";;;
60;"J42";"PinSocket_1x01_P2.54mm_Vertical";1;"Dia_z";;;
61;"J43";"PinSocket_1x08_P2.54mm_Vertical";1;"z-Step_High";;;
62;"J45";"PinSocket_1x08_P2.54mm_Vertical";1;"e2-Step_Low";;;
63;"J47";"PinSocket_1x01_P2.54mm_Vertical";1;"Dia_e2";;;
64;"J48";"PinSocket_1x08_P2.54mm_Vertical";1;"e2-Step_High";;;
65;"J50";"PinSocket_1x08_P2.54mm_Vertical";1;"e3-Step_Low";;;
66;"J52";"PinSocket_1x01_P2.54mm_Vertical";1;"Dia_e3";;;
67;"J53";"PinSocket_1x08_P2.54mm_Vertical";1;"e3-Step_High";;;
68;"J56";"PinSocket_1x08_P2.54mm_Vertical";1;"e1-Step_Low";;;
69;"J58";"PinSocket_1x01_P2.54mm_Vertical";1;"Dia_e1";;;
70;"J59";"PinSocket_1x08_P2.54mm_Vertical";1;"e1-Step_High";;;
71;"J8";"PinHeader_1x02_P2.54mm_Vertical";1;"Fan_Cooler";;;
72;"Q1";"TO-263-3_TabPin2";1;"HUF76439S3ST";;;
73;"Q3,Q4,Q5";"TO-263-3_TabPin2";3;"HUF76639S3ST";;;
74;"J19";"PinHeader_1x04_P2.54mm_Vertical";1;"SV";;;

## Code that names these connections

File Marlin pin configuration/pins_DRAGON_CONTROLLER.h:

/**
 * Marlin 3D Printer Firmware
 * Copyright (c) 2020 MarlinFirmware [https://github.com/MarlinFirmware/Marlin]
 *
 * Based on Sprinter and grbl.
 * Copyright (c) 2011 Camiel Gubbels / Erik van der Zalm
 *
 * This program is free software: you can redistribute it and/or modify
 * it under the terms of the GNU General Public License as published by
 * the Free Software Foundation, either version 3 of the License, or
 * (at your option) any later version.
 *
 * This program is distributed in the hope that it will be useful,
 * but WITHOUT ANY WARRANTY; without even the implied warranty of
 * MERCHANTABILITY or FITNESS FOR A PARTICULAR PURPOSE.  See the
 * GNU General Public License for more details.
 *
 * You should have received a copy of the GNU General Public License
 * along with this program.  If not, see <http://www.gnu.org/licenses/>.
 *
 */
#pragma once

#ifndef __STM32F1__
  #error "Oops! Select an STM32F1 board in 'Tools > Board.'"
#endif

/**
 * 2020 DocRaptor
 */

#define BOARD_INFO_NAME      "Dragon Controller"
#define DEFAULT_MACHINE_NAME "32bit powered"

#define DISABLE_JTAG
// Ignore temp readings during development.
//#define BOGUS_TEMPERATURE_GRACE_PERIOD 2000
#define FLASH_EEPROM_EMULATION
#define EEPROM_PAGE_SIZE     (0x800) // 2KB
#define EEPROM_START_ADDRESS uint32(0x8000000 + (STM32_FLASH_SIZE) * 1024 - 2 * EEPROM_PAGE_SIZE)
#define E2END                (EEPROM_PAGE_SIZE - 1)

//
// Limit Switches
//
#define X_MIN_PIN                           PC2
#define X_MAX_PIN                           PA2
#define Y_MIN_PIN                           PC1
#define Y_MAX_PIN                           PA1
#define Z_MIN_PIN                           PC0
#define Z_MAX_PIN                           PC3

//
// Steppers
//

#define X_STEP_PIN                          PC6
#define X_DIR_PIN                           PC7
#define X_ENABLE_PIN                        PB15

#define Y_STEP_PIN                          PB13
#define Y_DIR_PIN                           PB14
#define Y_ENABLE_PIN                        PB12

#define Z_STEP_PIN                          PB10
#define Z_DIR_PIN                           PB11
#define Z_ENABLE_PIN                        PB2

#define E0_STEP_PIN                         PC5
#define E0_DIR_PIN                          PB0
#define E0_ENABLE_PIN                       PC4


//
// Servos
//
#define SERVO0_PIN                          PA3


//
// Heaters / Fans
//
#define HEATER_0_PIN                        PA8
#define FAN_PIN                             PC8
#define HEATER_BED_PIN                      PC9

//
// Temperature Sensors
//
#define TEMP_BED_PIN                        PB1   // Analog Input
#define TEMP_0_PIN                          PA0   // Analog Input

//
// LCD Pins
//

/**
 *                _____                                             _____
 *            5V | · · | GND                                    5V | · · | GND
 *         RESET | · · | PB9 (SD_DETECT)             (LCD_D7) PC14 | · · | PC15 (LCD_D6)
 *  (MOSI)   PB5 | · · | PB8 (BTN_EN2)               (LCD_D5)  PB7 | · · | PC13 (LCD_D4)
 * (SD_SS)  PA15 | · · | PD2 (BTN_EN1)               (LCD_RS) PC12 | · · | PB6  (LCD_EN)
 *   (SCK)   PB3 | · · | PB4 (MISO)                 (BTN_ENC) PC11 | · · | PC10 (BEEPER)
 *                -----                                             -----
 *                EXP2                                              EXP1
 */

#if HAS_SPI_LCD
  #define BEEPER_PIN                     PC10
  #define BTN_ENC                        PC11

  #if ENABLED(CR10_STOCKDISPLAY)
    #define LCD_PINS_RS                  PC15

    #define BTN_EN1                      PB6
    #define BTN_EN2                      PC13

    #define LCD_PINS_ENABLE              PC14
    #define LCD_PINS_D4                  PB7
	
	#define LCD_PINS_D5                  PB7
    #define LCD_PINS_D6                  PC15
    #define LCD_PINS_D7                  PC14

  #else

    #define LCD_PINS_RS                  PC12

    #define BTN_EN1                      PD2
    #define BTN_EN2                      PB8

    #define LCD_PINS_ENABLE              PB6

	
    #define LCD_PINS_D4                  PC13
    
	#define LCD_PINS_D5                  PB7
    #define LCD_PINS_D6                  PC15
    #define LCD_PINS_D7                  PC14


  #endif

#endif // HAS_SPI_LCD


//
// SD Card and SPI
//

#define ENABLE_SPI3
#define SD_DETECT_PIN                     PB9
#define SCK_PIN                           PB3
#define MISO_PIN                          PB4
#define MOSI_PIN                          PB5
#define SS_PIN                            PA15

#if HAS_GRAPHICAL_LCD
  #define BOARD_ST7920_DELAY_1 DELAY_NS(125)
  #define BOARD_ST7920_DELAY_2 DELAY_NS(125)
  #define BOARD_ST7920_DELAY_3 DELAY_NS(125)
#endif

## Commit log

2020-02-25 First Version
    Upload of the first version
2020-02-27 License_CC_BY-SA.txt added
2020-02-27 Started to remove unneeded files
2020-03-12 Modified power and ground at the Mosfets
2020-03-18 New voltage regulators
    Replaced LM2575 with MP2451.
    Replaced AMS1117 with RT9013-33GB
2020-05-25 New Pinout and Marlin pin file
    Pinout, a marlin pin file and now being tested and most mistakes are corrected
